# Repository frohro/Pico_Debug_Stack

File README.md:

# Raspberry Pi Pico Debug Stack

**A professional-grade hardware interposer for debugging, analyzing, and validating Raspberry Pi Pico projects.**

## Overview

The **Pico Debug Stack** is a "Man-in-the-Middle" Debug tool designed to eliminate the wiring mess typically associated with hardware debugging.

It acts as a hardware shim:
1.  Unplug your **Target Pico (DUT)** from your project motherboard.
2.  Plug the **Debug Stack** into your motherboard.
3.  Plug your **Target Pico** into the socket on top of the Debug Stack.

With a single USB connection to your PC, you instantly gain access to a full suite of hardware analysis tools connected directly to the DUT's pins, with no breadboards or jumper wires required.

## Key Features

*   **Integrated Logic Analysis:** Onboard **RP2354B** (with 2MB internal flash) running **[Dr. Gusman's Logic Analyzer](https://github.com/gusmanb/logicanalyzer)**. Capable of capturing high-speed signals (SPI, I2C, UART, I2S) from the DUT.
*   **Integrated Debug Probe:** Onboard **RP2354B** (with 2MB internal flash) running **[Yapicoprobe](https://github.com/rgrr/yapicoprobe)** (compatible with standard CMSIS-DAP/Picoprobe). Provides SWD debugging (Step, Pause, Breakpoints) and a UART console.
*   **Hardware Stimulus:** The Debug Probe is hardwired to the DUT's GPIOs via protection resistors, allowing you to inject signals or simulate sensors programmatically.
*   **Integrated USB Hub:** An onboard **GL850G USB Hub** manages all devices via a single USB-C connection. It provides:
    *   Internal link to the Logic Analyzer.
    *   Internal link to the Debug Probe.
    *   **Two auxiliary USB-A ports** (Stacked Connector J10) for connecting the Target Pico or other peripherals.
*   **Robust Power:** A **2A Synchronous Buck Converter (MT2492)** ensures ample power for the Debug Stack and the Target Pico.
*   **Universal Compatibility:** Supports Raspberry Pi Pico, Pico W, Pico 2, and Pico 2W.
*   **Safety First:** 330Ω series resistors protect all GPIO connections between the Analyzer, Probe, and DUT.

## Hardware Architecture

The board consists of three main controllers:

1.  **U1 (Logic Analyzer):** An **RP2354B** dedicated to monitoring DUT GPIOs.
2.  **U2 (Debug Probe):** An **RP2354B** handling SWD communication and Stimulus generation.
3.  **U3 (USB Hub):** A **GL850G** providing connectivity to U1, U2, and the auxiliary ports.

### The Stack Physical Layout
*   **Top:** Socket for DUT (Pico H footprint).
*   **Middle:** The Debug Stack PCB (Analyzer + Probe + Hub).
*   **Bottom:** Male Headers (plugs into your original project).

### Important Note on DUT USB
The **Target Pico's USB data lines (D+/D-)** are **NOT** routed through the stack headers to the Hub automatically.
*   **Debug/Analysis:** Works instantly via the shim headers.
*   **Target USB Data:** If your Target Pico runs code that requires USB connectivity (e.g., TinyUSB), you must use a short USB cable to connect the Target Pico's USB port to one of the **Auxiliary USB-A ports** on the Debug Stack.

## Software & Firmware

To use this board, the onboard RP2354s must be flashed with the following firmware:

*   **Logic Analyzer (U1):** [Download Dr. Gusman's LogicAnalyzer Firmware](https://github.com/gusmanb/logicanalyzer) Ensure you use the RP2350 build for this board.  Instead of shorting GPIO0 and GPIO1 to do burst capture, GPIO30 is connected to GPIO29.  These are  settings in the LogicAnalyzer_BoardSettings.h.  I will put the .uF2 file for this LogicAnalyzer on GitHub.
*   **Debug Probe (U2):** [Download Yapicoprobe Firmware](https://github.com/rgrr/yapicoprobe) (or the official Raspberry Pi `debugprobe` firmware).  

## Using the Stimulus Features

One of the most powerful features of this board is the ability to use the **Debug Probe (U2)** to "exercise" the **DUT**. Because the Probe's GPIOs are wired to the DUT's GPIOs (via 330Ω resistors), you can write software for the Probe to simulate external hardware.

### Concept
Instead of physically wiring a button or a sensor to your project to test it, you can tell the Probe to "pull Pin 15 High" or "Send a pulse on Pin 2".

### Example: Writing Stimulus Software
*The following is a MicroPython example. You can run this on the **Debug Probe (U2)** to test the DUT.*

**Scenario:** Your DUT code waits for a button press on `GP15` and then blinks an LED. You want to automate testing this.

1.  Flash **MicroPython** onto the **Debug Probe (U2)** (temporarily replacing the probe firmware).
2.  Run this script on U2:

```python
import machine
import time

# Note: Check the schematic for the specific mapping between Probe GPIO and DUT GPIO
# The mapping is scrambled to optimize PCB routing.
stimulus_pin = machine.Pin(15, machine.Pin.OUT) 

print("Starting Stimulus Test...")

while True:
    print("Simulating Button Press (High)...")
    stimulus_pin.value(1)
    time.sleep(0.5) # Hold for 500ms
    
    print("Simulating Release (Low)...")
    stimulus_pin.value(0)
    time.sleep(2.0) # Wait 2 seconds before next test
```

### Advanced Stimulus (C/C++)
For high-speed protocol simulation (e.g., simulating an SPI sensor sending data to the DUT), you should write a C/C++ program for the Probe using the Pico SDK.

**Skeleton Code for `main.c` on the Probe:**

```c
#include "pico/stdlib.h"
#include "hardware/gpio.h"

// Map of Probe Pins to DUT Pins (Refer to Schematic)
#define STIMULUS_PIN_A  10 
#define STIMULUS_PIN_B  11

void generate_fake_sensor_data() {
    // Bit-bang a protocol or toggle pins
    gpio_put(STIMULUS_PIN_A, 1);
    sleep_us(10);
    gpio_put(STIMULUS_PIN_A, 0);
}

int main() {
    stdio_init_all();
    
    gpio_init(STIMULUS_PIN_A);
    gpio_set_dir(STIMULUS_PIN_A, GPIO_OUT);

    while (1) {
        // Wait for a command from PC, or just run a loop
        generate_fake_sensor_data();
        sleep_ms(100);
    }
}
```
## Kicad Project
This Kicad project uses the CDFER [JLCPCB Library](https://github.com/CDFER/JLCPCB-Kicad-Library).  If you don't install it, the rules checker in EESchema will bark at you.  After installing it, you have to quit Kicad and start again.

## Setup Instructions

1.  **Assembly:** Ensure U1 and U2 are flashed with their respective firmware.
2.  **Connection:** Plug the board into your PC via the USB-C port labeled `USB IN`.
3.  **Drivers:**
    *   **Analyzer:** Open Dr. Gusman's software (or Sigrok PulseView) and connect to the Logic Analyzer device.
    *   **Probe:** In VS Code (or your IDE), select the CMSIS-DAP interface for the Debug Probe.
4.  **Hardware Install:**
    *   Plug the Debug Stack into your project board.
    *   Plug your Pico H (DUT) into the socket on the Debug Stack.

## License

Designed by Rob Frohne, Walla Walla University.
Open Source Hardware.

---
*Note: This design uses RP2354B chips. Ensure your software toolchain supports the RP2350 architecture.*

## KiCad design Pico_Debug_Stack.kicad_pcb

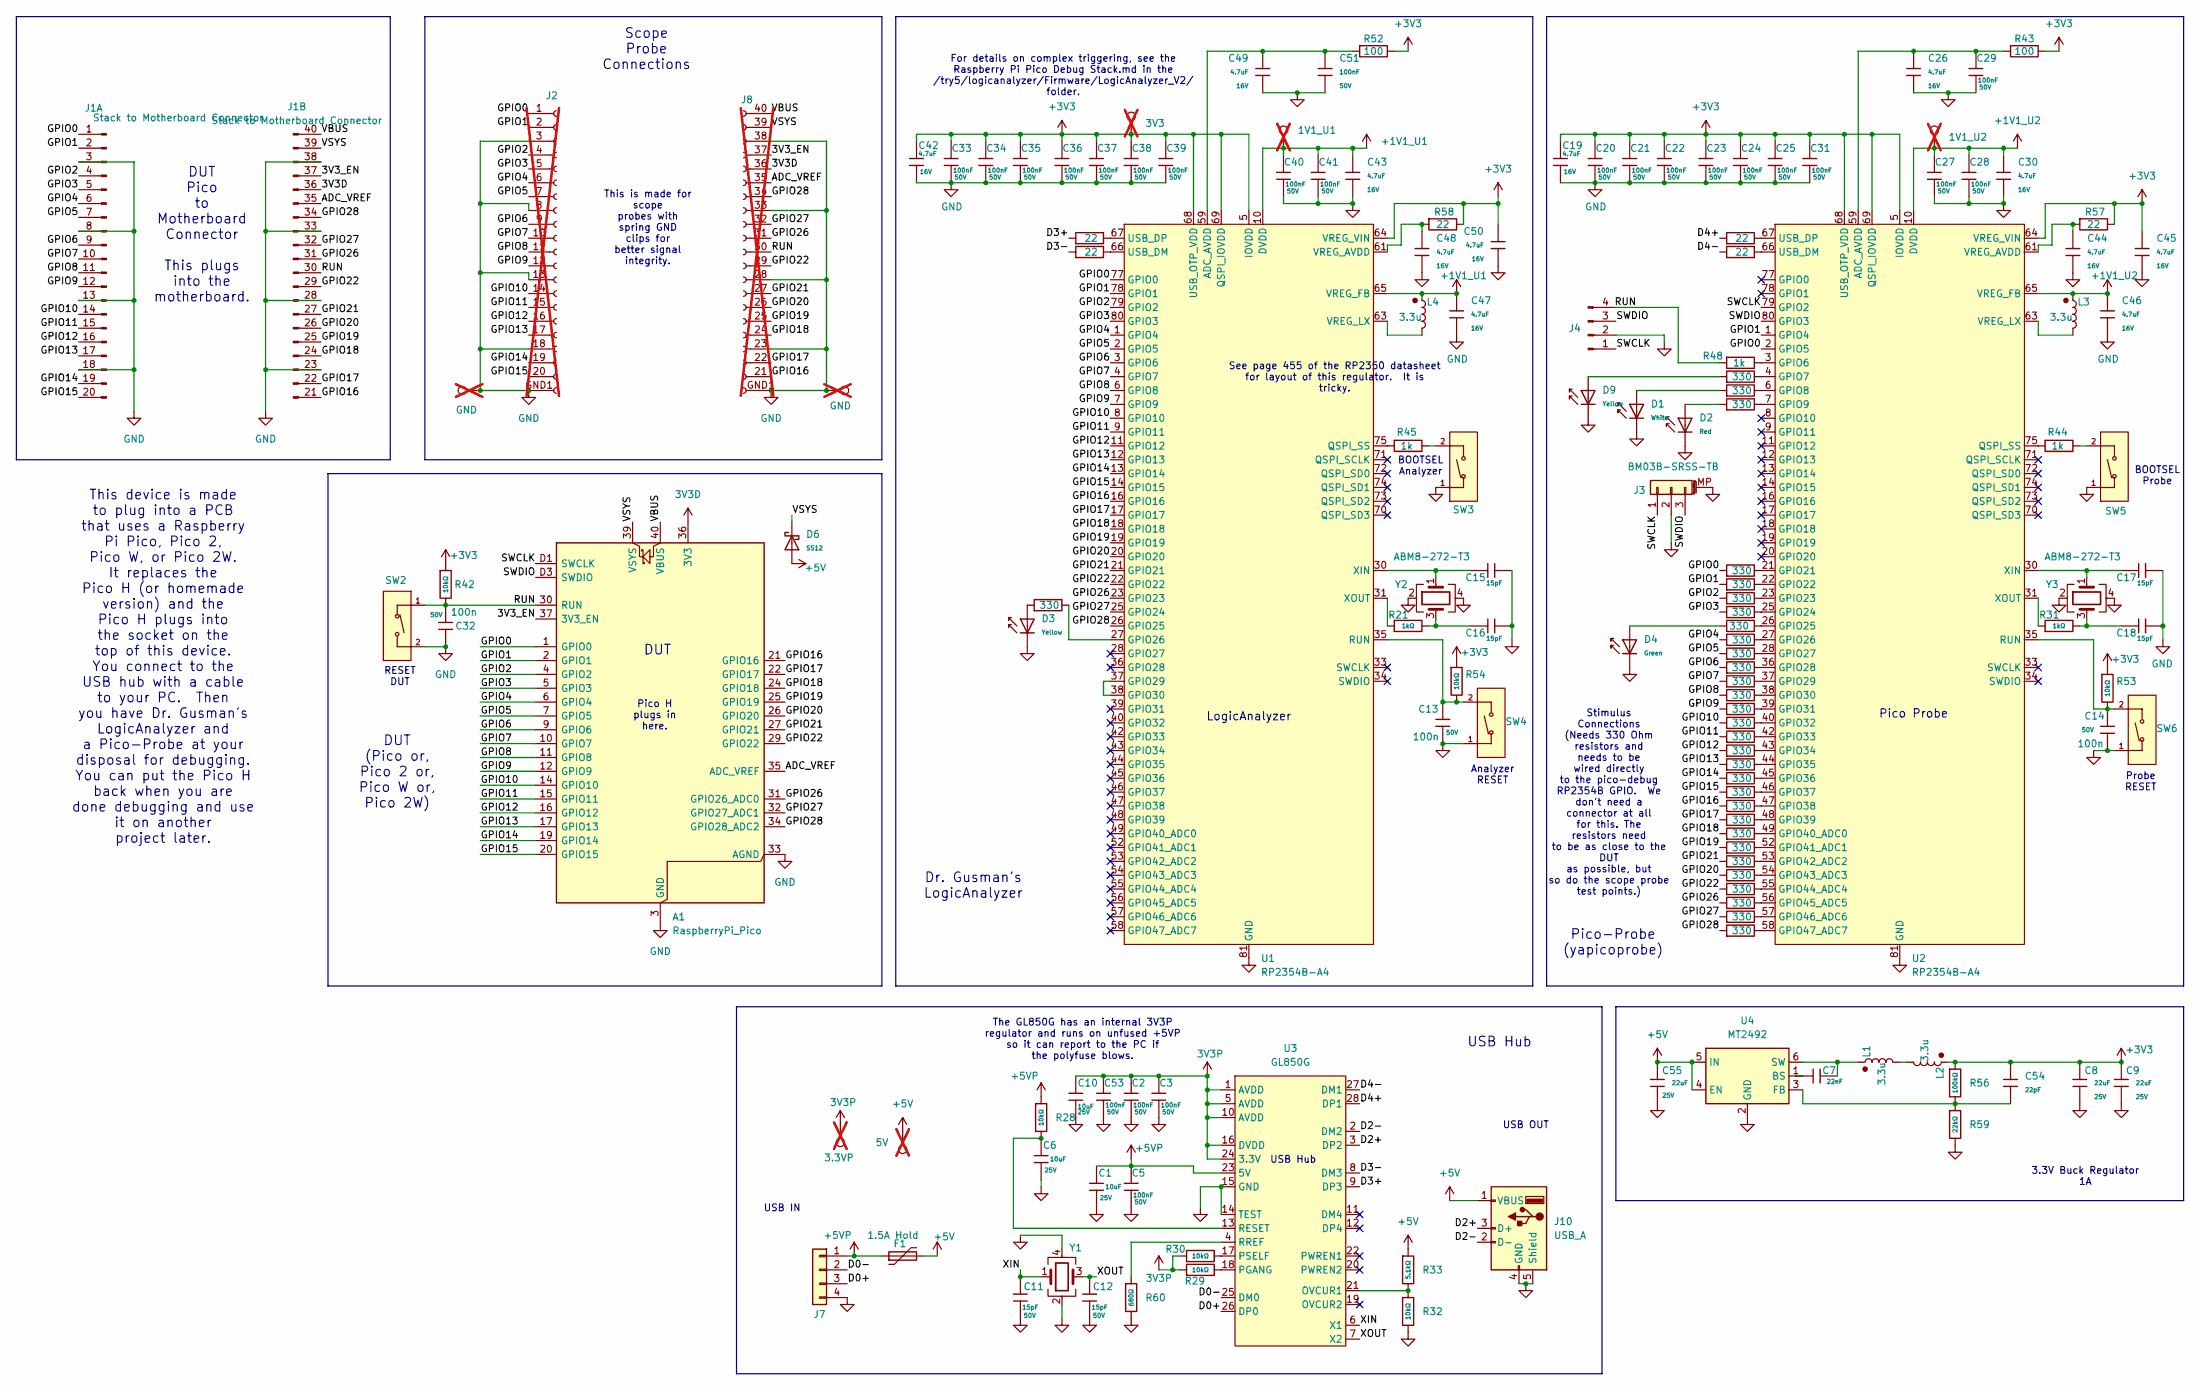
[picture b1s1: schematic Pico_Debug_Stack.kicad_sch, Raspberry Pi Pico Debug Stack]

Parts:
1V1_U1: 1V1_U1; TestPoint_Loop_D2.60mm_Drill0.9mm_Beaded; not fitted
A1: RaspberryPi_Pico; Pico Connector_SW
C1, C6, C10: 10uF; C_0603; Voltage Rated 25V; Tolerance ±20%; Part CL10A106MA8NRNC; LCSC C96446
C2, C3, C5, C20, C21, C22, C23, C24, C25, C27, C28, C29, C31, C33, C34, C35, C36, C37, C38, C39, C40, C41, C51, C53: 100nF; C_0603; Voltage Rated 50V; Tolerance ±10%; Part CC0603KRX7R9BB104; LCSC C14663
C7: 22nF; C_0603; Voltage Rated 50V; Tolerance ±10%; Part CL10B223KB8NNNC; LCSC C21122
C8, C9, C55: 22uF; C_0805; Voltage Rated 25V; Tolerance ±20%; Part CL21A226MAQNNNE; LCSC C45783
C11, C12, C15, C16, C17, C18: 15pF; C_0603; Voltage Rated 50V; Tolerance ±5%; Part CL10C150JB8NNNC; LCSC C1644
C13, C14, C32: 100n; C_0603; Voltage Rated 50V; Tolerance ±10%; Part CC0603KRX7R9BB104; LCSC C14663
C19, C26, C30, C42, C43, C44, C45, C46, C47, C48, C49, C50: 4.7uF; C_0603; Voltage Rated 16V; Tolerance ±10%; Part CL10A475KO8NNNC; LCSC C19666
C54: 22pF; C_0603; Voltage Rated 50V; Tolerance ±5%; Part CL10C220JB8NNNC; LCSC C1653
D1: White; D_0805; Part KT-0805W; LCSC C34499
D2: Red; D_0805; Forward Voltage (VF) 1.6V~2.6V; Part NCD0805R1; LCSC C84256
D3: Yellow; D_0603; Forward Voltage (VF) 1.6V~2.6V; Part NCD0603Y2; LCSC C89811
D4: Green; D_0805; Part KT-0805G; LCSC C2297
D6: SS12; D_SMA; Part SS12; LCSC C18199177
D9: Yellow; D_0805; Part KT-0805Y; LCSC C2296
F1: 1.5A Hold; Fuse_1206_3216Metric; LCSC C495353
J1: Stack to Motherboard Connector; Pico Connector; LCSC C5156618
J2: Scope_TP; Scope_Probe_GND_SPRING_01x20; not fitted
J3: BM03B-SRSS-TB; JST_SH_BM03B-SRSS-TB_1x03-1MP_P1.00mm_Vertical; MPN BM03B-SRSS-TB; LCSC C160389
J4: Conn_01x04_Pin; PinHeader_1x04_P2.54mm_Vertical
J7: Conn_01x04; SIP-4
J8: Scope_TP_21-40; Scope_Probe_GND_SPRING_01x21-40; not fitted
J10: USB_A; USB_AF_SMD; LCSC C112455
L1, L2, L3, L4: 3.3u; L_pol_2016; MPN MLP2016H3R3MT0S1 (substituted AOTA-B201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; LCSC C42411119
R1, R8, R9, R12, R13, R14, R15, R16, R17, R18, R19, R20, R22, R23, R24, R25, R26, R27, R34, R35, R36, R37, R38, R39, R40, R41, R46, R47, R49, R50, R51: 330; R_0603; Overload Voltage (Max) 75V; Tolerance ±1%; Part 0603WAF3300T5E; LCSC C23138
R4, R5, R6, R7: 22; R_0603; Overload Voltage (Max) 75V; Tolerance ±1%; Part 0603WAF220JT5E; LCSC C23345
R21, R31: 1kΩ; R_0603; Overload Voltage (Max) 75V; Tolerance ±1%; Part 0603WAF1001T5E; LCSC C21190
R28, R29, R30, R32, R42, R53, R54: 10kΩ; R_0603; Overload Voltage (Max) 75V; Tolerance ±1%; Part 0603WAF1002T5E; LCSC C25804
R33: 5.1kΩ; R_0603; Overload Voltage (Max) 75V; Tolerance ±1%; Part 0603WAF5101T5E; LCSC C23186
R43, R52: 100; R_0603; Tolerance ±1%; Overload Voltage (Max) 75V; MPN RC0402FR-07100RL; LCSC C22775
R44, R45, R48: 1k; R_0603; Tolerance ±1%; Overload Voltage (Max) 75V; MPN RC0402FR-071KL; LCSC C21190
R56: 100kΩ; R_0603; Overload Voltage (Max) 75V; Tolerance ±1%; Part 0603WAF1003T5E; LCSC C25803
R57, R58: 22; R_0603; Tolerance ±1%; Overload Voltage (Max) 75V; MPN RC0402FR-0727RL; LCSC C23345
R59: 22kΩ; R_0603; Overload Voltage (Max) 75V; Tolerance ±1%; Part 0603WAF2202T5E; LCSC C31850
R60: 680Ω; R_0603; Overload Voltage (Max) 75V; Tolerance ±1%; Part 0603WAF6800T5E; LCSC C23228
SW2, SW3, SW4, SW5, SW6: Tactile Button, 160gf; SW_TS-1088-AR02016; Voltage Rating (Dc) 12V; Part TS-1088-AR02016; LCSC C720477
TP1, TP2: GND; TestPoint_Loop_D2.54mm_Drill1.5mm_Beaded; not fitted
TP3: 5V; TestPoint_Loop_D2.50mm_Drill1.0mm_LowProfile; not fitted
TP4: 3V3; TestPoint_Loop_D2.60mm_Drill0.9mm_Beaded; not fitted
TP5: 1V1_U2; TestPoint_Loop_D2.60mm_Drill0.9mm_Beaded; not fitted
TP6: 3.3VP; TestPoint_Loop_D2.60mm_Drill0.9mm_Beaded; not fitted
U1, U2: RP2354B-A4; QFN-80-1EP_10x10mm_P0.4mm_EP3.4x3.4mm_ThermalVias; LCSC C39843328
U3: GL850G; SSOP-28_5.3x10.2mm_P0.65mm; LCSC C136617
U4: MT2492; SOT-23-6; LCSC C89358
Y1, Y2, Y3: ABM8-272-T3; Crystal_SMD_3225-4Pin_3.2x2.5mm; MPN ABM8-272-T3; LCSC C20625731

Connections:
3V3D: A1.36 (3V3), J1.36, J8.36
3V3P: C2.1, C3.1, C10.1, C53.1, R29.1, R30.1, TP6.1, U3.1 (AVDD), U3.5 (AVDD), U3.10 (AVDD), U3.16 (DVDD), U3.24 (3.3V)
+1V1_U1: 1V1_U1.1, C40.1, C41.1, C43.1, C47.1, L4.1, U1.10 (DVDD), U1.32 (DVDD), U1.51 (DVDD), U1.65 (VREG_FB)
+1V1_U2: C27.1, C28.1, C30.1, C46.1, L3.1, TP5.1, U2.10 (DVDD), U2.32 (DVDD), U2.51 (DVDD), U2.65 (VREG_FB)
+3V3: C8.1, C9.1, C19.1, C20.1, C21.1, C22.1, C23.1, C24.1, C25.1, C31.1, C33.1, C34.1, C35.1, C36.1, C37.1, C38.1, C39.1, C42.1, C45.1, C50.1, C54.1, L2.1, R42.1, R43.2, R52.2, R53.1, R54.1, R56.1, R57.2, R58.2, TP4.1, U1.5 (IOVDD), U1.15 (IOVDD), U1.24 (IOVDD), U1.29 (IOVDD), U1.41 (IOVDD), U1.50 (IOVDD), U1.60 (IOVDD), U1.64 (VREG_VIN), U1.68 (USB_OTP_VDD), U1.69 (QSPI_IOVDD), U1.76 (IOVDD), U2.5 (IOVDD), U2.15 (IOVDD), U2.24 (IOVDD), U2.29 (IOVDD), U2.41 (IOVDD), U2.50 (IOVDD), U2.60 (IOVDD), U2.64 (VREG_VIN), U2.68 (USB_OTP_VDD), U2.69 (QSPI_IOVDD), U2.76 (IOVDD)
+5V: C55.1, D6.2, F1.2, J10.1 (VBUS), R33.1, TP3.1, U4.4 (EN), U4.5 (IN)
+5VP: C1.1, C5.1, F1.1, J7.1, R28.1, U3.23 (5V)
/3V3_EN: A1.37 (3V3_EN), J1.37, J8.37 (Pin_.7)
/ADC_VREF: A1.35 (ADC_VREF), J1.35, J8.35
/D0+: J7.3, U3.26 (DP0)
/D0-: J7.2, U3.25 (DM0)
/D2+: J10.3 (D+), U3.3 (DP2)
/D2-: J10.2 (D-), U3.2 (DM2)
/D3+: R6.1, U3.9 (DP3)
/D3-: R7.1, U3.8 (DM3)
/D4+: R4.1, U3.28 (DP1)
/D4-: R5.1, U3.27 (DM1)
/GPIO0: A1.1 (GPIO0), J1.1, J2.1, R8.1, U1.77 (GPIO0), U2.2 (GPIO5)
/GPIO1: A1.2 (GPIO1), J1.2, J2.2, R9.1, U1.78 (GPIO1), U2.1 (GPIO4)
/GPIO2: A1.4 (GPIO2), J1.4, J2.4, R12.1, U1.79 (GPIO2)
/GPIO3: A1.5 (GPIO3), J1.5, J2.5, R13.1, U1.80 (GPIO3)
/GPIO4: A1.6 (GPIO4), J1.6, J2.6, R14.1, U1.1 (GPIO4)
/GPIO5: A1.7 (GPIO5), J1.7, J2.7, R15.1, U1.2 (GPIO5)
/GPIO6: A1.9 (GPIO6), J1.9, J2.9, R16.1, U1.3 (GPIO6)
/GPIO7: A1.10 (GPIO7), J1.10, J2.10, R17.1, U1.4 (GPIO7)
/GPIO8: A1.11 (GPIO8), J1.11, J2.11, R18.1, U1.6 (GPIO8)
/GPIO9: A1.12 (GPIO9), J1.12, J2.12, R19.1, U1.7 (GPIO9)
/GPIO10: A1.14 (GPIO10), J1.14, J2.14, R20.1, U1.8 (GPIO10)
/GPIO11: A1.15 (GPIO11), J1.15, J2.15, R22.1, U1.9 (GPIO11)
/GPIO12: A1.16 (GPIO12), J1.16, J2.16, R23.1, U1.11 (GPIO12)
/GPIO13: A1.17 (GPIO13), J1.17, J2.17, R24.1, U1.12 (GPIO13)
/GPIO14: A1.19 (GPIO14), J1.19, J2.19, R25.1, U1.13 (GPIO14)
/GPIO15: A1.20 (GPIO15), J1.20, J2.20, R26.1, U1.14 (GPIO15)
/GPIO16: A1.21 (GPIO16), J1.21 (Pin_22), J8.21, R27.1, U1.16 (GPIO16)
/GPIO17: A1.22 (GPIO17), J1.22, J8.22, R34.1, U1.17 (GPIO17)
/GPIO18: A1.24 (GPIO18), J1.24, J8.24, R35.1, U1.18 (GPIO18)
/GPIO19: A1.25 (GPIO19), J1.25, J8.25, R36.1, U1.19 (GPIO19)
/GPIO20: A1.26 (GPIO20), J1.26, J8.26, R38.1, U1.20 (GPIO20)
/GPIO21: A1.27 (GPIO21), J1.27, J8.27, R37.1, U1.21 (GPIO21)
/GPIO22: A1.29 (GPIO22), J1.29, J8.29, R39.1, U1.22 (GPIO22)
/GPIO26: A1.31 (GPIO26_ADC0), J1.31, J8.31, R40.1, U1.23 (GPIO23)
/GPIO27: A1.32 (GPIO27_ADC1), J1.32, J8.32, R41.1, U1.25 (GPIO24)
/GPIO28: A1.34 (GPIO28_ADC2), J1.34, J8.34, R1.1, U1.26 (GPIO25)
/RUN: A1.30 (RUN), C32.1, J1.30, J4.4, J8.30, R42.2, R48.1, SW2.1 (A)
/SWCLK: A1.D1 (SWCLK), J3.1, J4.1, U2.79 (GPIO2)
/SWDIO: A1.D3 (SWDIO), J3.3, J4.3, U2.80 (GPIO3)
/VBUS: A1.40 (VBUS), J1.40, J8.40
/VSYS: A1.39 (VSYS), D6.1, J1.39, J8.39
/XIN: C11.1, U3.6 (X1), Y1.1
/XOUT: C12.1, U3.7 (X2), Y1.3
GND: A1.3 (GND), A1.8 (GND), A1.13 (GND), A1.18 (GND), A1.23 (GND), A1.28 (GND), A1.33 (AGND), A1.38 (GND), A1.D2 (GND), C1.2, C2.2, C3.2, C5.2, C6.2, C8.2, C9.2, C10.2, C11.2, C12.2, C13.2, C14.2, C15.2, C16.2, C17.2, C18.2, C19.2, C20.2, C21.2, C22.2, C23.2, C24.2, C25.2, C26.2, C27.2, C28.2, C29.2, C30.2, C31.2, C32.2, C33.2, C34.2, C35.2, C36.2, C37.2, C38.2, C39.2, C40.2, C41.2, C42.2, C43.2, C44.2, C45.2, C46.2, C47.2, C48.2, C49.2, C50.2, C51.2, C53.2, C55.2, D1.1, D2.1, D3.1, D4.1, D9.1, J1.3, J1.8, J1.13, J1.18, J1.23, J1.28, J1.33, J1.38, J2.3, J2.8, J2.13, J2.18, J2.GND1 (GND), J3.2, J3.MP (MountPin), J4.2, J7.4, J8.23, J8.28, J8.33, J8.38, J8.GND1 (GND), J10.4 (GND), J10.5 (Shield), R32.2, R59.2, R60.2, SW2.2 (B), SW3.1 (A), SW4.1 (A), SW5.1 (A), SW6.1 (A), TP1.1, TP2.1, U1.62 (VREG_PGND), U1.81 (GND), U2.62 (VREG_PGND), U2.81 (GND), U3.14 (TEST), U3.15 (GND), U4.2 (GND), Y1.2, Y1.4, Y2.2, Y2.4, Y3.2, Y3.4
unnamed: C16.1, R21.2, Y2.3
unnamed: C18.1, R31.2, Y3.3
unnamed: D1.2, R50.1
unnamed: D2.2, R51.1
unnamed: D3.2, R46.1
unnamed: D4.2, R47.2
unnamed: D9.2, R49.1
unnamed: L1.2, L2.2
unnamed: R45.2, SW3.2 (B)
unnamed: C13.1, R54.2, SW4.2 (B), U1.35 (RUN)
unnamed: R44.2, SW5.2 (B)
unnamed: C14.1, R53.2, SW6.2 (B), U2.35 (RUN)
unnamed: C49.1, C51.1, R52.1, U1.59 (ADC_AVDD)
unnamed: R46.2, U1.27 (GPIO26)
unnamed: U1.37 (GPIO29), U1.38 (GPIO30)
unnamed: R45.1, U1.75 (QSPI_SS)
unnamed: R7.2, U1.66 (USB_DM)
unnamed: R6.2, U1.67 (USB_DP)
unnamed: C48.1, R58.1, U1.61 (VREG_AVDD)
unnamed: L4.2, U1.63 (VREG_LX)
unnamed: C15.1, U1.30 (XIN), Y2.1
unnamed: R21.1, U1.31 (XOUT)
unnamed: C26.1, C29.1, R43.1, U2.59 (ADC_AVDD)
unnamed: R48.2, U2.3 (GPIO6)
unnamed: R49.2, U2.4 (GPIO7)
unnamed: R50.2, U2.6 (GPIO8)
unnamed: R51.2, U2.7 (GPIO9)
unnamed: R8.2, U2.21 (GPIO21)
unnamed: R9.2, U2.22 (GPIO22)
unnamed: R12.2, U2.23 (GPIO23)
unnamed: R13.2, U2.25 (GPIO24)
unnamed: R47.1, U2.26 (GPIO25)
unnamed: R14.2, U2.27 (GPIO26)
unnamed: R15.2, U2.28 (GPIO27)
unnamed: R16.2, U2.36 (GPIO28)
unnamed: R17.2, U2.37 (GPIO29)
unnamed: R18.2, U2.38 (GPIO30)
unnamed: R19.2, U2.39 (GPIO31)
unnamed: R20.2, U2.40 (GPIO32)
unnamed: R22.2, U2.42 (GPIO33)
unnamed: R23.2, U2.43 (GPIO34)
unnamed: R24.2, U2.44 (GPIO35)
unnamed: R25.2, U2.45 (GPIO36)
unnamed: R26.2, U2.46 (GPIO37)
unnamed: R27.2, U2.47 (GPIO38)
unnamed: R34.2, U2.48 (GPIO39)
unnamed: R35.2, U2.49 (GPIO40_ADC0)
unnamed: R36.2, U2.52 (GPIO41_ADC1)
unnamed: R37.2, U2.53 (GPIO42_ADC2)
unnamed: R38.2, U2.54 (GPIO43_ADC3)
unnamed: R39.2, U2.55 (GPIO44_ADC4)
unnamed: R40.2, U2.56 (GPIO45_ADC5)
unnamed: R41.2, U2.57 (GPIO46_ADC6)
unnamed: R1.2, U2.58 (GPIO47_ADC7)
unnamed: R44.1, U2.75 (QSPI_SS)
unnamed: R5.2, U2.66 (USB_DM)
unnamed: R4.2, U2.67 (USB_DP)
unnamed: C44.1, R57.1, U2.61 (VREG_AVDD)
unnamed: L3.2, U2.63 (VREG_LX)
unnamed: C17.1, U2.30 (XIN), Y3.1
unnamed: R31.1, U2.31 (XOUT)
unnamed: R32.1, R33.2, U3.21 (OVCUR1)
unnamed: R29.2, U3.18 (PGANG)
unnamed: R30.2, U3.17 (PSELF)
unnamed: C6.1, R28.2, U3.13 (RESET)
unnamed: R60.1, U3.4 (RREF)
unnamed: C7.1, U4.1 (BS)
unnamed: C54.2, R56.2, R59.1, U4.3 (FB)
unnamed: C7.2, L1.1, U4.6 (SW)

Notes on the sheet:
Stimulus Connections (Needs 330 Ohm resistors and needs to be wired directly to the pico-debug RP2354B GPIO. We don't need a connector at all for this. The resistors need to be as close to the DUT as possible, but so do the scope probe test points.)
Dr. Gusman's LogicAnalyzer
USB IN
RESET DUT
DUT (Pico or, Pico 2 or, Pico W or, Pico 2W)
Pico H plugs in here.
LogicAnalyzer
USB Hub
BOOTSEL Analyzer
Analyzer RESET
Pico-Probe (yapicoprobe)
See page 455 of the RP2350 datasheet for layout of this regulator. It is tricky.
DUT
Pico Probe
Scope Probe Connections
This device is made to plug into a PCB that uses a Raspberry Pi Pico, Pico 2, Pico W, or Pico 2W. It replaces the Pico H (or homemade version) and the Pico H plugs into the socket on the top of this device. You connect to the USB hub with a cable to your PC. Then you have Dr. Gusman's LogicAnalyzer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
For details on complex triggering, see the Raspberry Pi Pico Debug Stack.md in the /try5/logicanalyzer/Firmware/LogicAnalyzer_V2/ folder.
3.3V Buck Regulator 1A
This is made for scope probes with spring GND clips for better signal integrity.
USB OUT
BOOTSEL Probe
Probe RESET
The GL850G has an internal 3V3P regulator and runs on unfused +5VP so it can report to the PC if the polyfuse blows.
DUT Pico to Motherboard Connector This plugs into the motherboard.

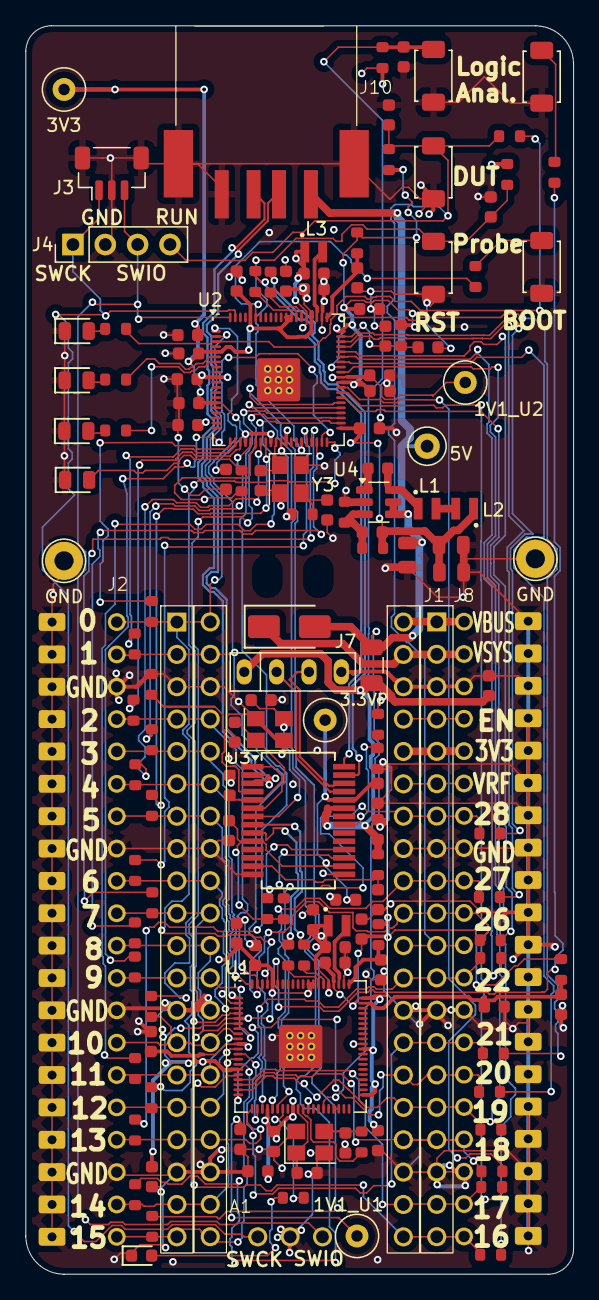
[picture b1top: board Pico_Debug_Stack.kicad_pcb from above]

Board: 4 copper layers, 43.0 x 98.0 mm, 146 parts (1 on the bottom side), 120 nets.

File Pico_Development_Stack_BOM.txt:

"Reference","Value","DNP","Footprint","Datasheet","LCSC"
"Y1,Y2,Y3","ABM8-272-T3","","Crystal:Crystal_SMD_3225-4Pin_3.2x2.5mm","https://jlcpcb.com/api/file/downloadByFileSystemAccessId/855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","C20625731"
"U4","MT2492","","Package_TO_SOT_SMD:SOT-23-6","https://jlcpcb.com/api/file/downloadByFileSystemAccessId/858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","C89358"
"U3","GL850G","","Package_SO:SSOP-28_5.3x10.2mm_P0.65mm","https://www.lcsc.com/datasheet/C136617.pdf","C136617"
"U1,U2","RP2354B","","rpi-lib-kicad-rp235x:QFN-80-1EP_10x10mm_P0.4mm_EP3.4x3.4mm_ThermalVias","https://datasheets.raspberrypi.com/rp2350/rp2350-datasheet.pdf","C39843328"
"TP5","1V1_U2","","TestPoint:TestPoint_Loop_D2.50mm_Drill1.0mm_LowProfile","~",""
"TP4","3V3","","TestPoint:TestPoint_Loop_D2.50mm_Drill1.0mm_LowProfile","~",""
"TP3","5V","","TestPoint:TestPoint_Loop_D2.50mm_Drill1.0mm_LowProfile","~",""
"TP2","GND Wire 0","","TestPoint:TestPoint_Loop_D2.54mm_Drill1.5mm_Beaded","~",""
"TP1","GND Wire 1","","TestPoint:TestPoint_Loop_D2.54mm_Drill1.5mm_Beaded","~",""
"SW1","SPDT","","rpi-lib-kicad-rp235x:SW_SPDT_Shouhan_MSK12C02","https://www.lcsc.com/datasheet/C431540.pdf","C431540"
"S1,S2,S3,S4,S5","Tactile Button, 160gf","","PCM_JLCPCB:SW_TS-1088-AR02016","https://www.lcsc.com/datasheet/lcsc_datasheet_2304140030_XUN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","C720477"
"R60","680Ω","","PCM_JLCPCB:R_0603","https://www.lcsc.com/datasheet/lcsc_datasheet_2206010100_UNI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","C23228"
"R59","22kΩ","","PCM_JLCPCB:R_0603","https://www.lcsc.com/datasheet/lcsc_datasheet_2206010030_UNI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","C31850"
"R56","100kΩ","","PCM_JLCPCB:R_0603","https://www.lcsc.com/datasheet/lcsc_datasheet_2206010045_UNI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","C25803"
"R44,R45,R48","1k","","PCM_JLCPCB:R_0603","https://www.lcsc.com/datasheet/lcsc_datasheet_2206010130_UNI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","C21190"
"R43,R52","100","","PCM_JLCPCB:R_0603","https://www.lcsc.com/datasheet/lcsc_datasheet_2411221126_UNI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","C22775"
"R28,R29,R30,R32,R42,R53,R54","10kΩ","","PCM_JLCPCB:R_0603","https://www.lcsc.com/datasheet/lcsc_datasheet_2206010045_UNI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","C25804"
"R21,R31","1kΩ","","PCM_JLCPCB:R_0603","https://www.lcsc.com/datasheet/lcsc_datasheet_2206010130_UNI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","C21190"
"R10,R11,R33","5.1kΩ","","PCM_JLCPCB:R_0603","https://www.lcsc.com/datasheet/lcsc_datasheet_2206010116_UNI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","C23186"
"R4,R5,R6,R7,R57,R58","22","","PCM_JLCPCB:R_0603","https://www.lcsc.com/datasheet/lcsc_datasheet_2206010100_UNI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","C23345"
"R1,R2,R3,R8,R9,R12,R13,R14,R15,R16,R17,R18,R19,R20,R22,R23,R24,R25,R26,R27,R34,R35,R36,R37,R38,R39,R40,R41,R46,R47,R49,R50,R51","330","","PCM_JLCPCB:R_0603","https://www.lcsc.com/datasheet/lcsc_datasheet_2206010116_UNI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","C23138"
"L1,L2,L3,L4","3.3u","","RP2350_60QFN_minimal:L_pol_2016","https://lcsc.com/datasheet/lcsc_datasheet_2412101620_ABRACON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","C42411119"
"J10","USB_A_Stacked","","Connector_USB:USB_A_CUI_UJ2-ADH-TH_Horizontal_Stacked","https://jlcpcb.com/api/file/downloadByFileSystemAccessId/858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","C698206"
"J7","Connector, USB-TYPE-C-16P","","PCM_JLCPCB:TYPE-C-SMD_HX-TYPE-C-16PIN","https://atta.szlcsc.com/upload/public/pdf/source/20220920/0E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","C2927039"
"J4","Conn_01x04_Pin","DNP","Connector_PinHeader_2.54mm:PinHeader_1x04_P2.54mm_Vertical","~",""
"J3,J5,J6,J9","Conn_01x03_Socket","DNP","Connector_PinHeader_2.54mm:PinHeader_1x03_P2.54mm_Vertical","~","C146243"
"J1,J2,J8","~","","Connector_PinHeader_2.54mm:PinHeader_1x20_P2.54mm_Vertical","","C5156618"
"F1","1.5A Hold","","Fuse:Fuse_1206_3216Metric","https://jlcpcb.com/api/file/downloadByFileSystemAccessId/858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","C495353"
"D7","BAT54","","PCM_JLCPCB:D_SOT-23","https://wmsc.lcsc.com/wmsc/upload/file/pdf/v2/lcsc/240617162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","C22466368"
"D6","DSL34","","PCM_JLCPCB:D_SOD-123FL","https://wmsc.lcsc.com/wmsc/upload/file/pdf/v2/lcsc/240617161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","C22466347"
"D5","Green","","PCM_JLCPCB:D_0805","https://www.lcsc.com/datasheet/lcsc_datasheet_1806151820_Hub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","C2297"
"D3,D4","Red","","PCM_JLCPCB:D_0603","https://www.lcsc.com/datasheet/lcsc_datasheet_1810231112_Hub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","C2286"
"D2","White","","PCM_JLCPCB:D_0603","https://www.lcsc.com/datasheet/lcsc_datasheet_2305091500_Hub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","C2290"
"D1","Yellow","","PCM_JLCPCB:D_0603","https://www.lcsc.com/datasheet/lcsc_datasheet_2008201033_Fos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","C89811"
"C54","22pF","","PCM_JLCPCB:C_0603","https://www.lcsc.com/datasheet/lcsc_datasheet_2304140030_Sam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","C1653"
"C19,C26,C30,C42,C43,C44,C45,C46,C47,C48,C49,C50","4.7uF","","PCM_JLCPCB:C_0603","https://www.lcsc.com/datasheet/lcsc_datasheet_2304140030_Sam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","C19666"
"C13,C14,C32","100n","","PCM_JLCPCB:C_0603","https://www.lcsc.com/datasheet/lcsc_datasheet_2211101700_YAG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","C14663"
"C11,C12,C15,C16,C17,C18","15pF","","PCM_JLCPCB:C_0603","https://www.lcsc.com/datasheet/lcsc_datasheet_2304140030_Sam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","C1644"
"C8,C9,C55","22uF","","PCM_JLCPCB:C_0805","https://www.lcsc.com/datasheet/lcsc_datasheet_2304140030_Sam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","C45783"
"C7","22nF","","PCM_JLCPCB:C_0603","https://www.lcsc.com/datasheet/lcsc_datasheet_2304140030_Sam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","C21122"
"C2,C3,C4,C5,C20,C21,C22,C23,C24,C25,C27,C28,C29,C31,C33,C34,C35,C36,C37,C38,C39,C40,C41,C51,C53","100nF","","PCM_JLCPCB:C_0603","https://www.lcsc.com/datasheet/lcsc_datasheet_2211101700_YAG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","C14663"
"C1,C6,C10","10uF","","PCM_JLCPCB:C_0603","https://www.lcsc.com/datasheet/lcsc_datasheet_2304140030_Sam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","C96446"
"A1","RaspberryPi_Pico","","Module:RaspberryPi_Pico_SMD_HandSolder","https://datasheets.raspberrypi.com/pico/pico-datasheet.pdf",""
"1V1_U1","1V1","","TestPoint:TestPoint_Loop_D2.50mm_Drill1.0mm_LowProfile","~",""

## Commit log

2025-12-30 Fixed the README.md
2025-12-30 Replace wrong version with Version 0.1.1
2025-12-30 removed possibly obsolete schematic png
2025-12-30 fixed url for yapicoprobe
2026-01-11 Added a power plate for 1V1_U1 and 1V1_U2 to the power layer
2026-04-01 Added holes for USB C socket
    Made this v0.1.2
2026-04-14 note about USB C cables

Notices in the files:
README.md:
License: MIT
